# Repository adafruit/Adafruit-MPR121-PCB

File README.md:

## Adafruit MPR121 capacitive touch breakout PCB
<a href="http://www.adafruit.com/products/1982"><br/>
Click here to purchase one from the Adafruit shop</a>
<a href="http://www.adafruit.com/products/4830"><br/>
Click here to purchase one from the Adafruit shop</a>

Add lots of touch sensors to your next microcontroller project with this easy-to-use 12-channel capacitive touch sensor breakout board, starring the MPR121. This chip can handle up to 12 individual touch pads.

The MPR121 has support for only I2C, which can be implemented with nearly any microcontroller. You can select one of 4 addresses with the ADDR pin (or two on the Gator version), for a total of 48 (24 on the Gator version) capacitive touch pads on one I2C 2-wire bus. Using this chip is a lot easier than doing the capacitive sensing with analog inputs: it handles all the filtering for you and can be configured for more/less sensitivity.

This sensor comes as a tiny hard-to-solder chip so we put it onto a breakout board for you. Since it's a 3V-only chip, we added a 3V regulator and I2C level shifting so its safe to use with any 3V or 5V microcontroller/processor like Arduino. We even added an LED onto the IRQ line so it will blink when touches are detected, making debugging by sight a bit easier on you. Comes with a fully assembled board, and a stick of 0.1" header so you can plug it into a breadboard. For contacts, we suggest using copper foil or pyralux, then solder a wire that connects from the foil pad to the breakout.

To make using the MPR121 QT Gator as easy as possible, we’ve put the MPR121 on a breakout PCB in our Stemma QT form factor with a sprinkle of support circuitry to give you options when testing. You can either use a breadboard or the SparkFun qwiic compatible STEMMA QT connectors, and compatibility with 5V voltage levels as commonly found on Arduinos, as well as 3.3V logic used by many other boards like the Raspberry Pi or our Feathers. QT Cable is not included, but we have a variety in the shop for quick plug-and-play support.

PCB files for Adafruit MPR121 capacitive touch breakout. The format is EagleCAD schematic and board layout
- https://www.adafruit.com/product/1982
- https://www.adafruit.com/product/4830

### License

Adafruit invests time and resources providing this open source design, please support Adafruit and open-source hardware by purchasing products from [Adafruit](https://www.adafruit.com)!

All text above must be included in any redistribution

Designed by Limor Fried/Ladyada for Adafruit Industries.
Creative Commons Attribution/Share-Alike, all text above must be included in any redistribution.
See license.txt for additional information.

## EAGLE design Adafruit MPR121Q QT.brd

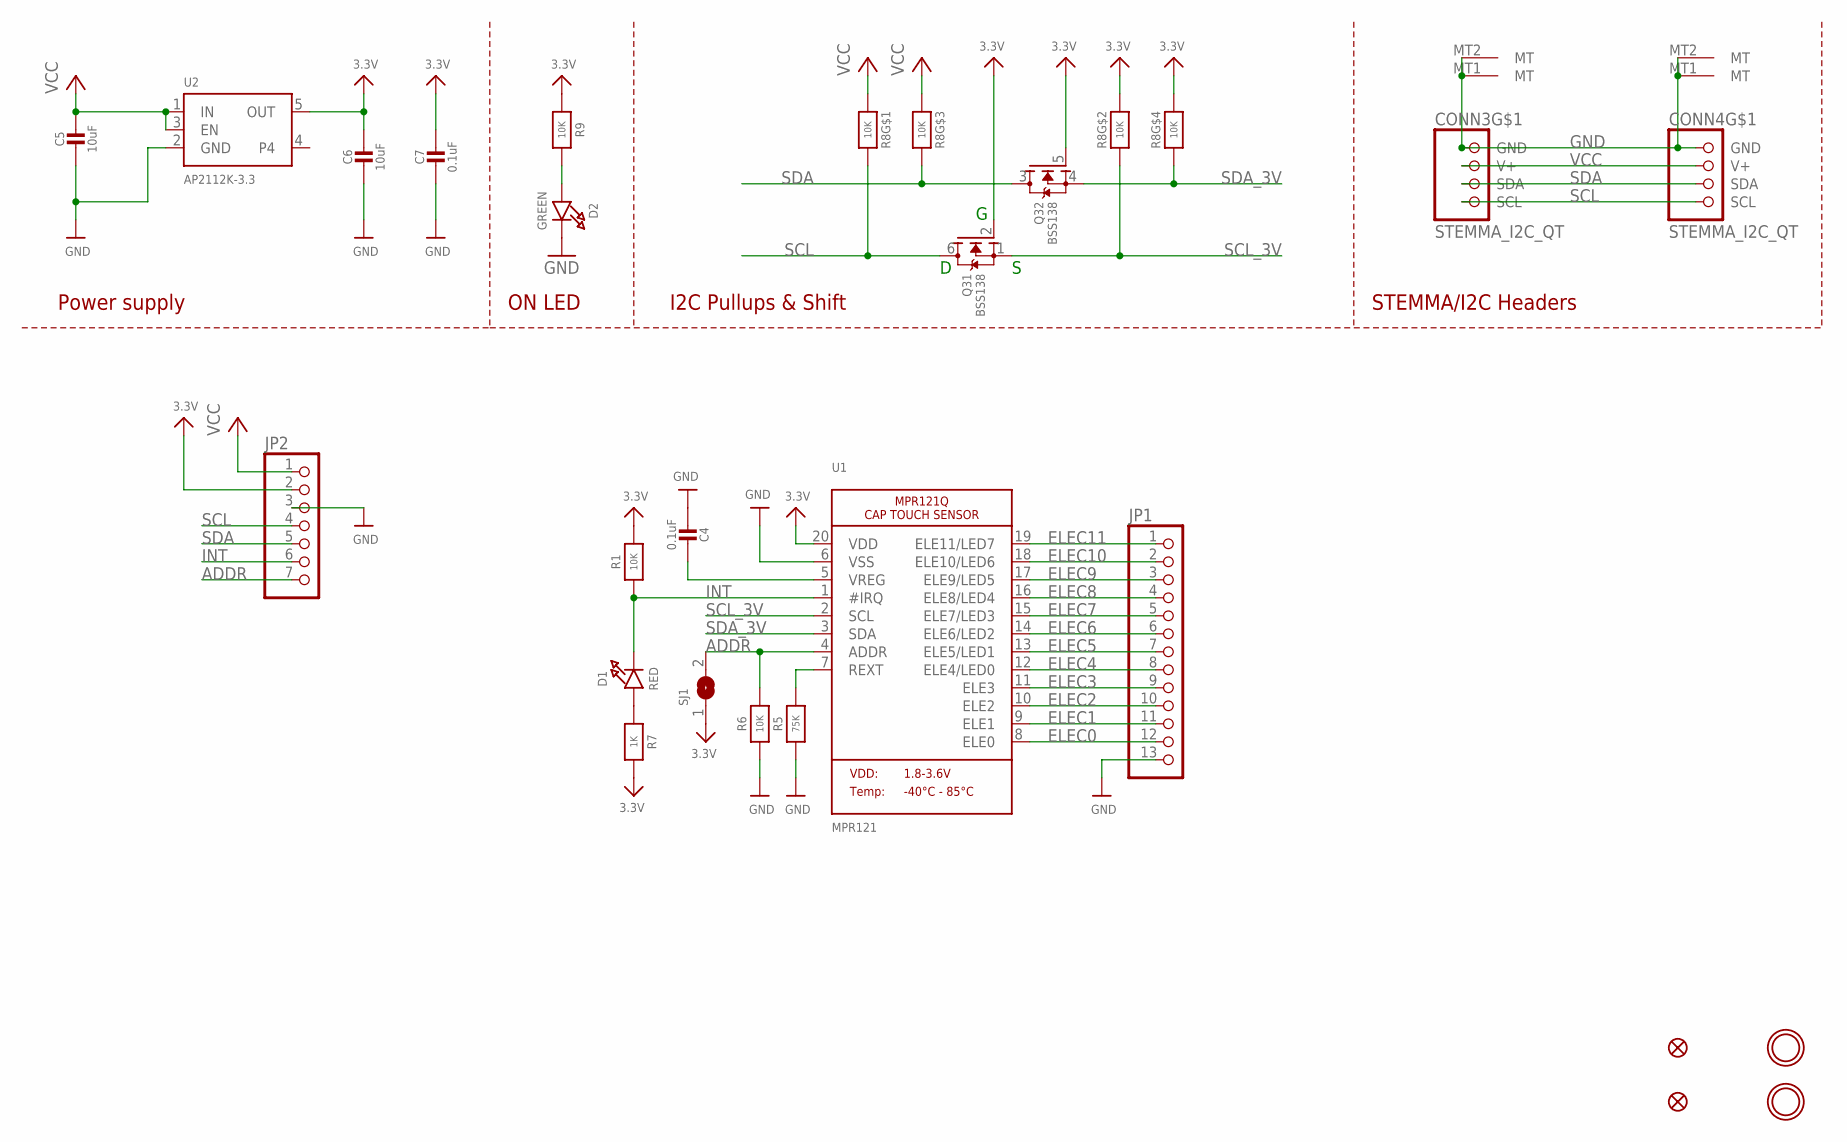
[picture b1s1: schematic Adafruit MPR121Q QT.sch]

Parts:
C4, C7: 0.1uF; 0603-NO
C5, C6: 10uF; 0805-NO
CONN3, CONN4: STEMMA_I2C_QT; JST_SH4
D1: RED; CHIPLED_0603_NOOUTLINE
D2: GREEN; CHIPLED_0603_NOOUTLINE
FID3, FID4: FIDUCIAL_1MM
JP1: HEADER-1X13; 1X13_ROUND_70
JP2: HEADER-1X770MIL; 1X07_ROUND_70
Q3: BSS138; SOT363
R1, R6, R9: 10K; 0603-NO
R5: 75K; 0603-NO
R7: 1K; 0603-NO
R8: 10K; RESPACK_4X0603
SJ1: SOLDERJUMPER; SOLDERJUMPER_ARROW_NOPASTE
U1: MPR121; QFN20_3MM_NOTHERMAL
U2: AP2112K-3.3; SOT23-5
U$34, U$35: MOUNTINGHOLE2.5; MOUNTINGHOLE_2.5_PLATED

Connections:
3.3V: C6.1, C7.1, JP2.2, Q3.2 (G), Q3.5 (G), R1.2, R7.2, R8.2 (1), R8.4 (1), R9.1, SJ1.1, U1.20 (VDD), U2.5 (OUT)
ADDR: JP2.7, R6.2, SJ1.2, U1.4 (ADDR)
ELEC0: JP1.12, U1.8 (ELE0)
ELEC1: JP1.11, U1.9 (ELE1)
ELEC2: JP1.10, U1.10 (ELE2)
ELEC3: JP1.9, U1.11 (ELE3)
ELEC4: JP1.8, U1.12 (ELE4/LED0)
ELEC5: JP1.7, U1.13 (ELE5/LED1)
ELEC6: JP1.6, U1.14 (ELE6/LED2)
ELEC7: JP1.5, U1.15 (ELE7/LED3)
ELEC8: JP1.4, U1.16 (ELE8/LED4)
ELEC9: JP1.3, U1.17 (ELE9/LED5)
ELEC10: JP1.2, U1.18 (ELE10/LED6)
ELEC11: JP1.1, U1.19 (ELE11/LED7)
GND: C4.2, C5.2, C6.2, C7.2, CONN3.1 (GND), CONN3.MT1 (MT), CONN3.MT2 (MT), CONN4.1 (GND), CONN4.MT1 (MT), CONN4.MT2 (MT), D2.C, JP1.13, JP2.3, R5.1, R6.1, U1.6 (VSS), U2.2 (GND)
INT: D1.C, JP2.6, R1.1, U1.1 (#IRQ)
unnamed: D1.A, R7.1
unnamed: C4.1, U1.5 (VREG)
unnamed: R5.2, U1.7 (REXT)
unnamed: D2.A, R9.2
SCL: CONN3.4 (SCL), CONN4.4 (SCL), JP2.4, Q3.6 (D), R8.8 (2)
SCL_3V: Q3.1 (S), R8.7 (2), U1.2 (SCL)
SDA: CONN3.3 (SDA), CONN4.3 (SDA), JP2.5, Q3.3 (D), R8.6 (2)
SDA_3V: Q3.4 (S), R8.5 (2), U1.3 (SDA)
VCC: C5.1, CONN3.2 (V+), CONN4.2 (V+), JP2.1, R8.1, R8.3 (1), U2.1 (IN), U2.3 (EN)

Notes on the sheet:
I2C Pullups & Shift
STEMMA/I2C Headers
ON LED
Power supply

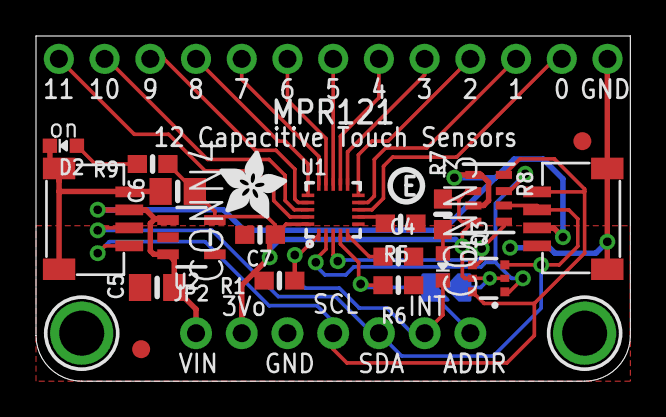
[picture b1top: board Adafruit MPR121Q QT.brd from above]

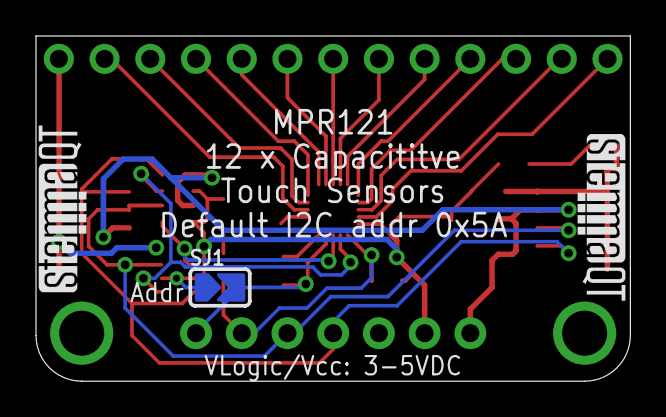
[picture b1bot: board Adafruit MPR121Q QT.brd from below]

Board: 2 copper layers, 33.0 x 19.2 mm, 28 parts (3 on the bottom side), 25 nets.

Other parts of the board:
U$9: PCBFEAT-REV-040
U$37: ADAFRUIT_3.5MM
U$39, U$40: STEMMAQT

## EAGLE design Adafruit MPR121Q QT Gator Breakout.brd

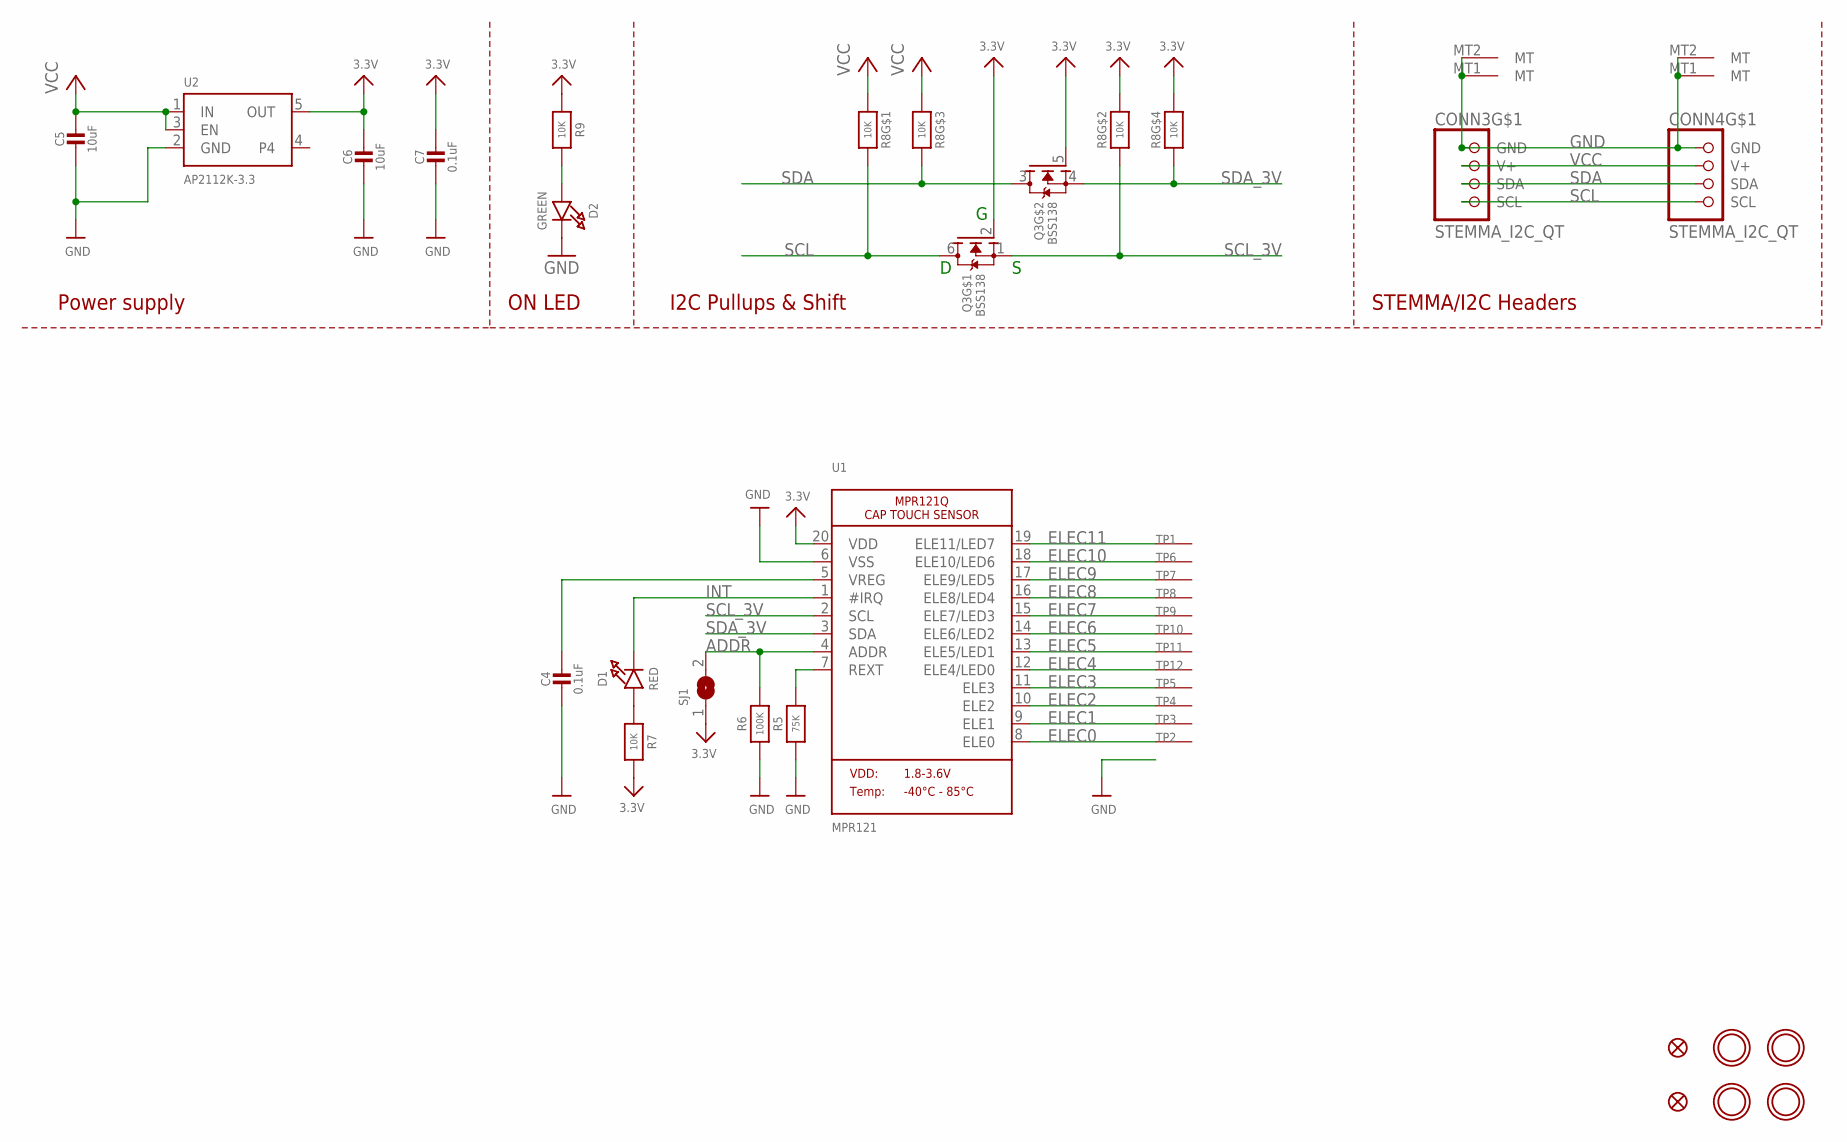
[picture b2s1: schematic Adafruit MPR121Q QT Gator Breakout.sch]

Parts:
C4, C7: 0.1uF; 0603-NO
C5, C6: 10uF; 0805-NO
CONN3, CONN4: STEMMA_I2C_QT; JST_SH4
D1: RED; CHIPLED_0603_NOOUTLINE
D2: GREEN; CHIPLED_0603_NOOUTLINE
FID3, FID4: FIDUCIAL_1MM
Q3: BSS138; SOT363
R5: 75K; 0603-NO
R6: 100K; 0603-NO
R7, R9: 10K; 0603-NO
R8: 10K; RESPACK_4X0603
SJ1: SOLDERJUMPER; SOLDERJUMPER_ARROW_NOPASTE
TP1, TP2, TP3, TP4, TP5, TP6, TP7, TP8, TP9, TP10, TP11, TP12: SEWTAPPCB_ALLIGATOR; PCB_ALLI
U1: MPR121; QFN20_3MM_NOTHERMAL
U2: AP2112K-3.3; SOT23-5
U$7, U$8, U$34, U$35: MOUNTINGHOLE2.5; MOUNTINGHOLE_2.5_PLATED

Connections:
3.3V: C6.1, C7.1, Q3.2 (G), Q3.5 (G), R7.2, R8.2 (1), R8.4 (1), R9.1, SJ1.1, U1.20 (VDD), U2.5 (OUT)
ADDR: R6.2, SJ1.2, U1.4 (ADDR)
ELEC0: TP2.P$1, U1.8 (ELE0)
ELEC1: TP3.P$1, U1.9 (ELE1)
ELEC2: TP4.P$1, U1.10 (ELE2)
ELEC3: TP5.P$1, U1.11 (ELE3)
ELEC4: TP12.P$1, U1.12 (ELE4/LED0)
ELEC5: TP11.P$1, U1.13 (ELE5/LED1)
ELEC6: TP10.P$1, U1.14 (ELE6/LED2)
ELEC7: TP9.P$1, U1.15 (ELE7/LED3)
ELEC8: TP8.P$1, U1.16 (ELE8/LED4)
ELEC9: TP7.P$1, U1.17 (ELE9/LED5)
ELEC10: TP6.P$1, U1.18 (ELE10/LED6)
ELEC11: TP1.P$1, U1.19 (ELE11/LED7)
GND: C4.2, C5.2, C6.2, C7.2, CONN3.1 (GND), CONN3.MT1 (MT), CONN3.MT2 (MT), CONN4.1 (GND), CONN4.MT1 (MT), CONN4.MT2 (MT), D2.C, R5.1, R6.1, U1.6 (VSS), U2.2 (GND)
INT: D1.C, U1.1 (#IRQ)
unnamed: D1.A, R7.1
unnamed: C4.1, U1.5 (VREG)
unnamed: R5.2, U1.7 (REXT)
unnamed: D2.A, R9.2
SCL: CONN3.4 (SCL), CONN4.4 (SCL), Q3.6 (D), R8.8 (2)
SCL_3V: Q3.1 (S), R8.7 (2), U1.2 (SCL)
SDA: CONN3.3 (SDA), CONN4.3 (SDA), Q3.3 (D), R8.6 (2)
SDA_3V: Q3.4 (S), R8.5 (2), U1.3 (SDA)
VCC: C5.1, CONN3.2 (V+), CONN4.2 (V+), R8.1, R8.3 (1), U2.1 (IN), U2.3 (EN)

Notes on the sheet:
I2C Pullups & Shift
STEMMA/I2C Headers
ON LED
Power supply

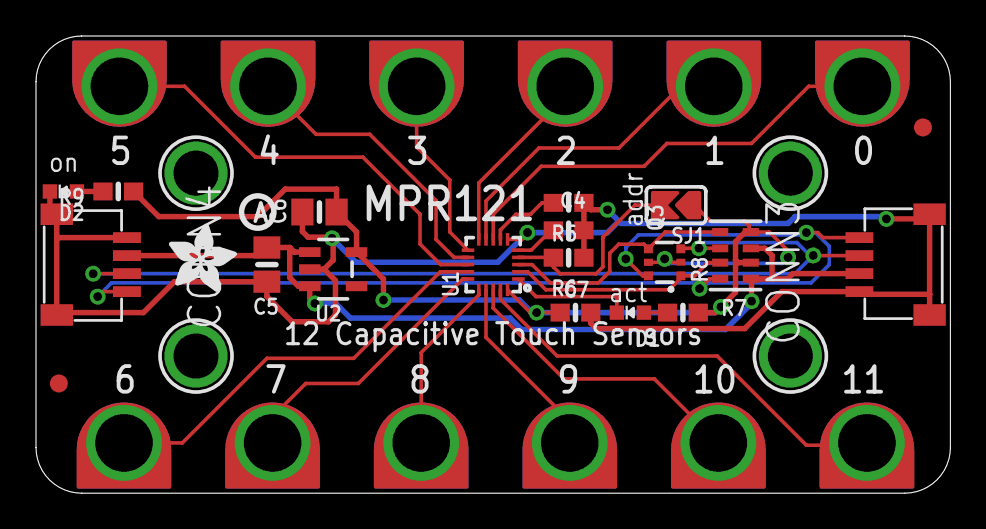
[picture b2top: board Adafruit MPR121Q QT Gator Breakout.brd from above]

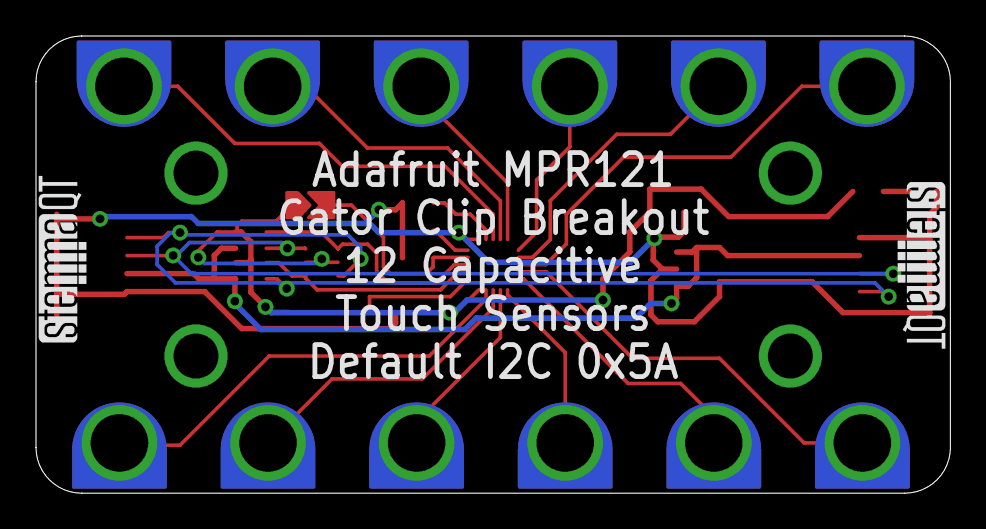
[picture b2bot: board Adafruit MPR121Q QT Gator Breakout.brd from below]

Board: 2 copper layers, 50.8 x 25.4 mm, 39 parts (2 on the bottom side), 25 nets.

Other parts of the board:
U$10: PCBFEAT-REV-040
U$37: ADAFRUIT_3.5MM
U$39, U$40: STEMMAQT

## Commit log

2015-08-27 mpr121 breakout
2020-12-30 Adding Gator board files.
2021-01-26 Adding asset.
2021-01-26 Adding board files.
2021-01-26 Update image.

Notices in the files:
parts and their libraries:
microbuilder: This work is placed in the public domain, and may be freely used for commercial and non-commercial work with the following conditions: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
